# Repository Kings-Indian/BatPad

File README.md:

# BatPad
Batpad is a macropad based off batman. It has 2 rotatory encoders, 4 keys, and 2 leds, making it look somewhat like a drone controller which is somwhat the intended long-term purpose. 

##  Bill of Materials (BOM)

| **Item**                         | **Quantity** | **Notes**                    |
|----------------------------------|--------------|------------------------------|
| Seeed XIAO RP2040               | 1            | Microcontroller              |
| MX-Style switches               | 3            | Mechanical key switches      |
| EC11 Rotary Encoders            | 2            | With push-button function    |
| Blank DSA Keycaps (White)       | 3            | Compatible with MX switches  |
| M3x16mm Screws                  | 8            | For mounting components      |
| M3x5mmx4mm Heatset Inserts      | 8            | For threaded support in plastic |

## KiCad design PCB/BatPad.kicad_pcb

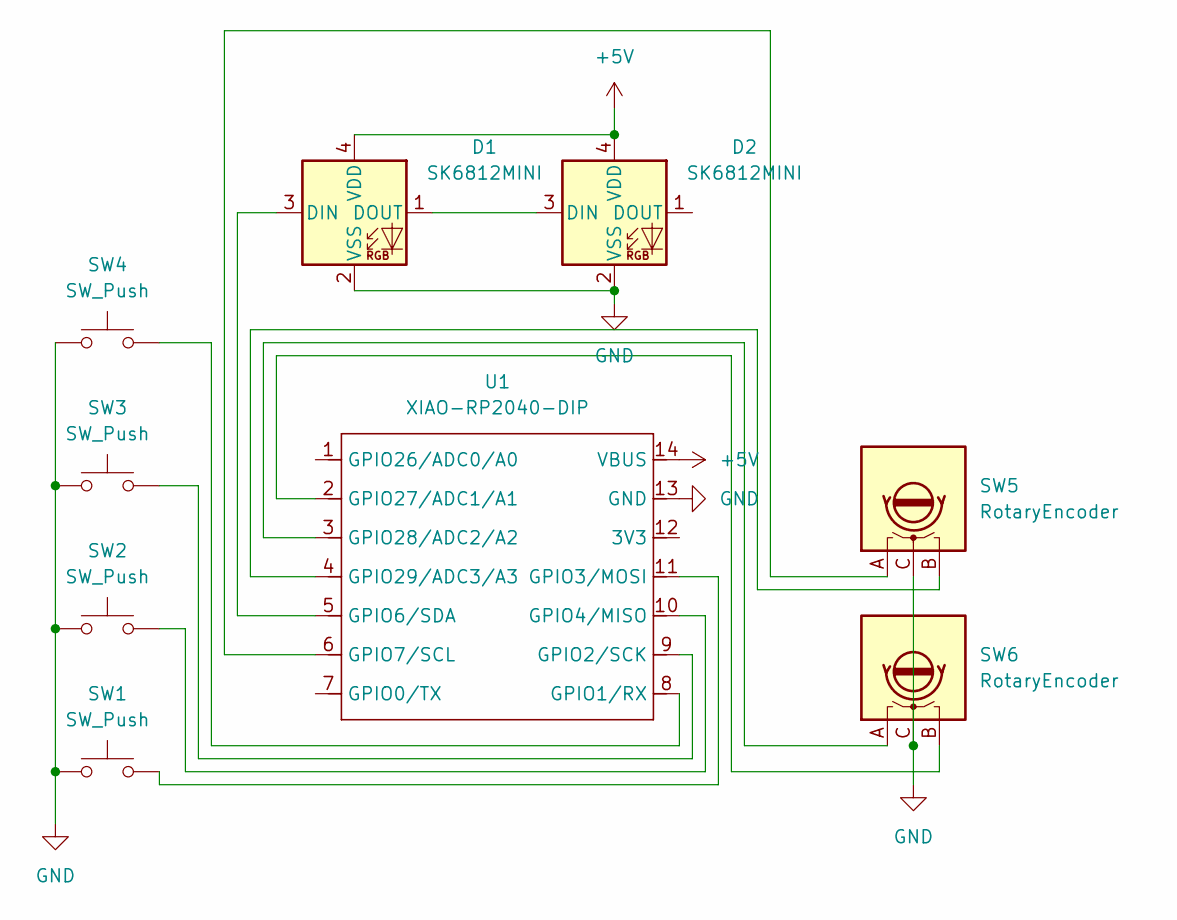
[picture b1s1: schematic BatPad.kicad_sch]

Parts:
D1, D2: SK6812MINI; LED_SK6812MINI_PLCC4_3.5x3.5mm_P1.75mm
SW1, SW2, SW3, SW4: SW_Push; SW_Cherry_MX_1.00u_PCB
SW5, SW6: RotaryEncoder; RotaryEncoder_Alps_EC11E_Vertical_H20mm
U1: XIAO-RP2040-DIP

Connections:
+5V: D1.4 (VDD), D2.4 (VDD), U1.14 (VBUS)
GND: D1.2 (VSS), D2.2 (VSS), SW1.1, SW2.1, SW3.1, SW4.1, SW5.C, SW6.C, U1.13 (GND)
unnamed: D1.3 (DIN), U1.5 (GPIO6/SDA)
unnamed: D1.1 (DOUT), D2.3 (DIN)
unnamed: SW4.2, U1.8 (GPIO1/RX)
unnamed: SW3.2, U1.9 (GPIO2/SCK)
unnamed: SW1.2, U1.11 (GPIO3/MOSI)
unnamed: SW2.2, U1.10 (GPIO4/MISO)
unnamed: SW5.A, U1.6 (GPIO7/SCL)
unnamed: SW6.B, U1.2 (GPIO27/ADC1/A1)
unnamed: SW6.A, U1.3 (GPIO28/ADC2/A2)
unnamed: SW5.B, U1.4 (GPIO29/ADC3/A3)

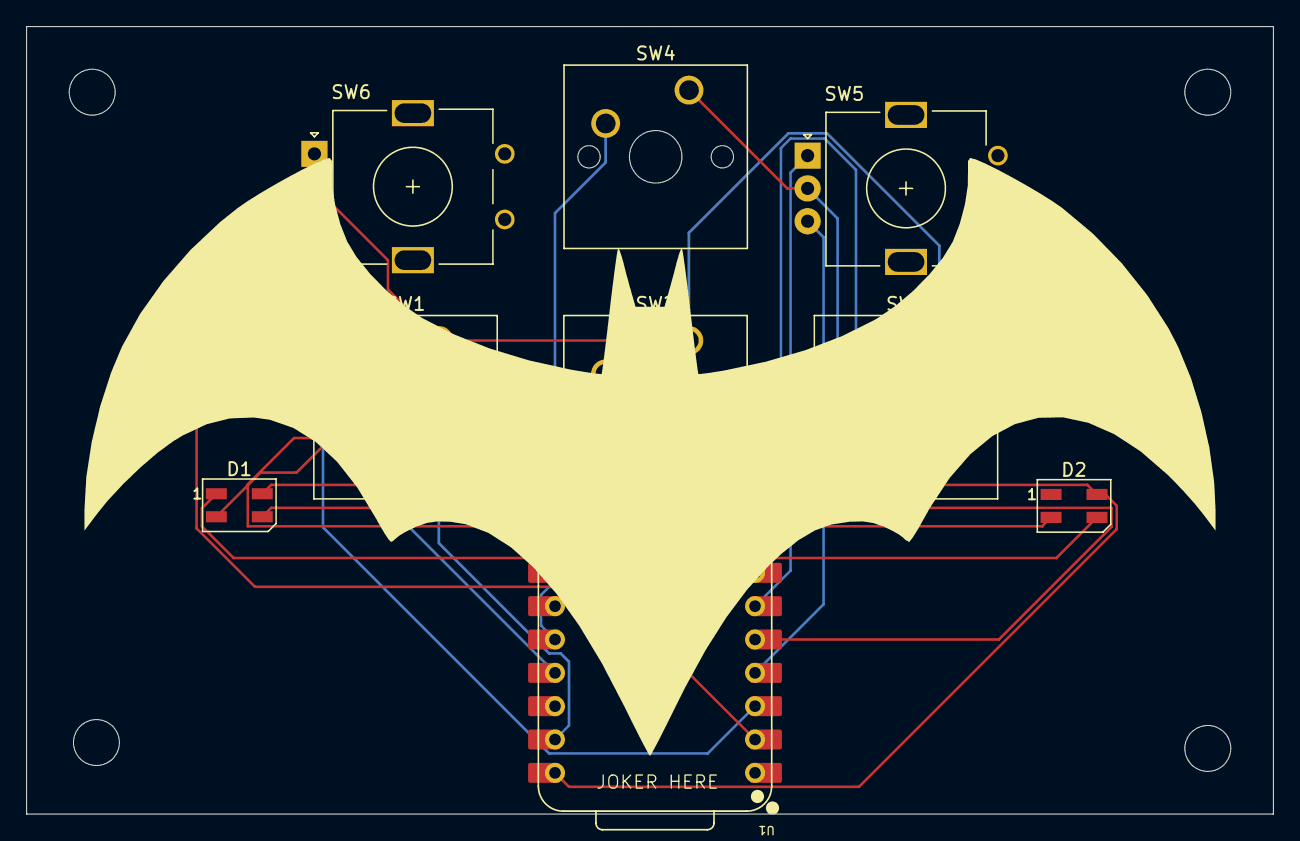
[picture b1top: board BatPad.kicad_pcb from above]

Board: 2 copper layers, 95.0 x 60.0 mm, 9 parts (0 on the bottom side), 12 nets.

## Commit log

2025-07-31 added stuff my head hurts ivent slept dfor so long gahhh
2025-08-01 added schematic
2025-08-02 fixed schematic (gnd anf 5v)
